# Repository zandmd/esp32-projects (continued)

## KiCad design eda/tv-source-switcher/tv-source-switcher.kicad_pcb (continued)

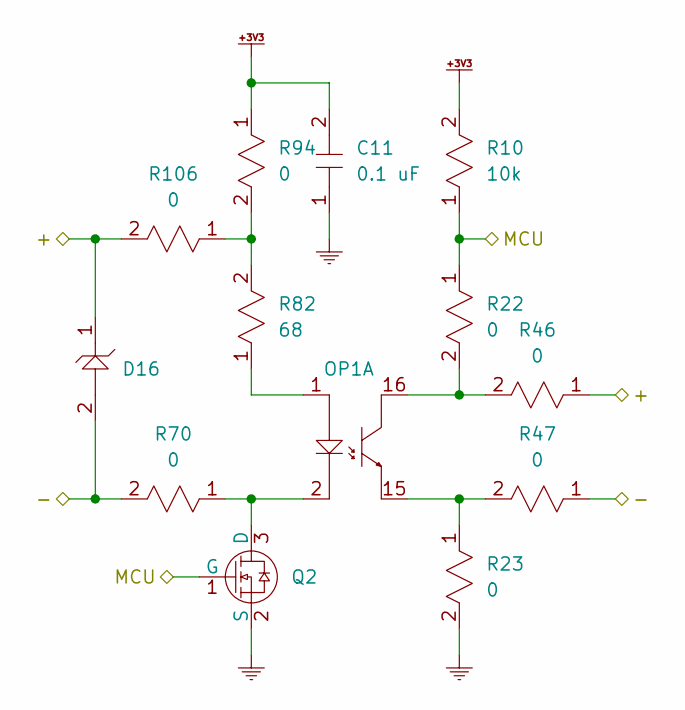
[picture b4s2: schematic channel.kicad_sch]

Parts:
C11: 0.1 uF; PASSIVE-NPOL-0805
D16: SMAJ5.0A
OP1: LTV-847S
Q2: BSS816NWH6327XTSA1
R10: 10k; PASSIVE-NPOL-0805
R22, R23, R46, R47, R70, R94, R106: 0; PASSIVE-NPOL-0805
R82: 68; PASSIVE-NPOL-0805

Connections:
+3V3: C11.2, R10.2, R94.1; also elsewhere on the board
/Channel 0/MCU: Q2.1 (G), R10.1, R22.1; also elsewhere on the board
GND: C11.1, Q2.2 (S), R23.2; also elsewhere on the board
unnamed: OP1.1 (A), R82.1
unnamed: OP1.16 (C), R22.2, R46.2
unnamed: OP1.15 (E), R23.1, R47.2
unnamed: OP1.2 (K), Q2.3 (D), R70.1
unnamed 52: OP1.3 (A); also elsewhere on the board
unnamed 53: OP1.14 (C); also elsewhere on the board
unnamed 54: OP1.13 (E); also elsewhere on the board
unnamed 55: OP1.4 (K); also elsewhere on the board
unnamed 56: OP1.5 (A); also elsewhere on the board
unnamed 57: OP1.12 (C); also elsewhere on the board
unnamed 58: OP1.11 (E); also elsewhere on the board
unnamed 59: OP1.6 (K); also elsewhere on the board
unnamed 60: OP1.7 (A); also elsewhere on the board
unnamed 61: OP1.10 (C); also elsewhere on the board
unnamed 62: OP1.9 (E); also elsewhere on the board
unnamed 63: OP1.8 (K); also elsewhere on the board
unnamed: R82.2, R94.2, R106.1

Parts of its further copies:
C12, C13, C14, C15, C16, C17, C18, C19, C20, C21, C22: 0.1 uF; PASSIVE-NPOL-0805
D5, D6, D7, D8, D9, D10, D11, D12, D13, D14, D15: SMAJ5.0A
OP2, OP3: LTV-847S
Q3, Q4, Q5, Q6, Q7, Q8, Q9, Q10, Q11, Q12, Q13: BSS816NWH6327XTSA1
R11, R12, R13, R14, R15, R16, R17, R18, R19, R20, R21: 10k; PASSIVE-NPOL-0805
R24, R25, R26, R27, R28, R29, R30, R31, R32, R33, R34, R35, R36, R37, R38, R39, R40, R41, R42, R43, R44, R45, R48, R49, R50, R51, R52, R53, R54, R55, R56, R57, R58, R59, R60, R61, R62, R63, R64, R65, R66, R67, R68, R69, R71, R72, R73, R74, R75, R76, R77, R78, R79, R80, R81, R95, R96, R97, R98, R99, R100, R101, R102, R103, R104, R105, R107, R108, R109, R110, R111, R112, R113, R114, R115, R116, R117: 0; PASSIVE-NPOL-0805
R83, R84, R85, R86, R87, R88, R89, R90, R91, R92, R93: 68; PASSIVE-NPOL-0805

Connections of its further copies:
+3V3: C12.2, C13.2, C14.2, C15.2, C16.2, C17.2, C18.2, C19.2, C20.2, C21.2, C22.2, R11.2, R12.2, R13.2, R14.2, R15.2, R16.2, R17.2, R18.2, R19.2, R20.2, R21.2, R95.1, R96.1, R97.1, R98.1, R99.1, R100.1, R101.1, R102.1, R103.1, R104.1, R105.1; also elsewhere on the board
/Channel 1/+: D6.1, R48.1, R107.2; also elsewhere on the board
/Channel 1/-: D6.2, R49.1, R71.2; also elsewhere on the board
/Channel 1/MCU: Q3.1 (G), R11.1, R24.1; also elsewhere on the board
/Channel 2/+: D7.1, R50.1, R108.2; also elsewhere on the board
/Channel 2/-: D7.2, R51.1, R72.2; also elsewhere on the board
/Channel 2/MCU: Q4.1 (G), R12.1, R26.1; also elsewhere on the board
/Channel 3/+: D8.1, R52.1, R109.2; also elsewhere on the board
/Channel 3/-: D8.2, R53.1, R73.2; also elsewhere on the board
/Channel 3/MCU: Q5.1 (G), R13.1, R28.1; also elsewhere on the board
/Channel 4/+: D9.1, R54.1, R110.2; also elsewhere on the board
/Channel 4/-: D9.2, R55.1, R74.2; also elsewhere on the board
/Channel 4/MCU: Q6.1 (G), R14.1, R30.1; also elsewhere on the board
/Channel 5/+: D10.1, R56.1, R111.2; also elsewhere on the board
/Channel 5/-: D10.2, R57.1, R75.2; also elsewhere on the board
/Channel 5/MCU: Q7.1 (G), R15.1, R32.1; also elsewhere on the board
/Channel 6/+: D11.1, R58.1, R112.2; also elsewhere on the board
/Channel 6/-: D11.2, R59.1, R76.2; also elsewhere on the board
/Channel 6/MCU: Q8.1 (G), R16.1, R34.1; also elsewhere on the board
/Channel 7/+: D12.1, R60.1, R113.2; also elsewhere on the board
/Channel 7/-: D12.2, R61.1, R77.2; also elsewhere on the board
/Channel 7/MCU: Q9.1 (G), R17.1, R36.1; also elsewhere on the board
/Channel 8/+: D13.1, R62.1, R114.2; also elsewhere on the board
/Channel 8/-: D13.2, R63.1, R78.2; also elsewhere on the board
/Channel 8/MCU: Q10.1 (G), R18.1, R38.1; also elsewhere on the board
/Channel 9/+: D14.1, R64.1, R115.2; also elsewhere on the board
/Channel 9/-: D14.2, R65.1, R79.2; also elsewhere on the board
/Channel 9/MCU: Q11.1 (G), R19.1, R40.1; also elsewhere on the board
/Channel 10/+: D15.1, R66.1, R116.2; also elsewhere on the board
/Channel 10/-: D15.2, R67.1, R80.2; also elsewhere on the board
/Channel 10/MCU: Q12.1 (G), R20.1, R42.1; also elsewhere on the board
/Channel 11/MCU: Q13.1 (G), R21.1, R44.1; also elsewhere on the board
GND: C12.1, C13.1, C14.1, C15.1, C16.1, C17.1, C18.1, C19.1, C20.1, C21.1, C22.1, Q3.2 (S), Q4.2 (S), Q5.2 (S), Q6.2 (S), Q7.2 (S), Q8.2 (S), Q9.2 (S), Q10.2 (S), Q11.2 (S), Q12.2 (S), Q13.2 (S), R25.2, R27.2, R29.2, R31.2, R33.2, R35.2, R37.2, R39.2, R41.2, R43.2, R45.2; also elsewhere on the board
unnamed 52: R83.1; also elsewhere on the board
unnamed 53: R24.2, R48.2; also elsewhere on the board
unnamed 54: R25.1, R49.2; also elsewhere on the board
unnamed 55: Q3.3 (D), R71.1; also elsewhere on the board
unnamed 56: R84.1; also elsewhere on the board
unnamed 57: R26.2, R50.2; also elsewhere on the board
unnamed 58: R27.1, R51.2; also elsewhere on the board
unnamed 59: Q4.3 (D), R72.1; also elsewhere on the board
unnamed 60: R85.1; also elsewhere on the board
unnamed 61: R28.2, R52.2; also elsewhere on the board
unnamed 62: R29.1, R53.2; also elsewhere on the board
unnamed 63: Q5.3 (D), R73.1; also elsewhere on the board
unnamed: OP2.1 (A), R86.1
unnamed: OP2.16 (C), R30.2, R54.2
unnamed: OP2.15 (E), R31.1, R55.2
unnamed: OP2.2 (K), Q6.3 (D), R74.1
unnamed: OP2.3 (A), R87.1
unnamed: OP2.14 (C), R32.2, R56.2
unnamed: OP2.13 (E), R33.1, R57.2
unnamed: OP2.4 (K), Q7.3 (D), R75.1
unnamed: OP2.5 (A), R88.1
unnamed: OP2.12 (C), R34.2, R58.2
unnamed: OP2.11 (E), R35.1, R59.2
unnamed: OP2.6 (K), Q8.3 (D), R76.1
unnamed: OP2.7 (A), R89.1
unnamed: OP2.10 (C), R36.2, R60.2
unnamed: OP2.9 (E), R37.1, R61.2
unnamed: OP2.8 (K), Q9.3 (D), R77.1
unnamed: OP3.1 (A), R90.1
unnamed: OP3.16 (C), R38.2, R62.2
unnamed: OP3.15 (E), R39.1, R63.2
unnamed: OP3.2 (K), Q10.3 (D), R78.1
unnamed: OP3.3 (A), R91.1
unnamed: OP3.14 (C), R40.2, R64.2
unnamed: OP3.13 (E), R41.1, R65.2
unnamed: OP3.4 (K), Q11.3 (D), R79.1
unnamed: OP3.5 (A), R92.1
unnamed: OP3.12 (C), R42.2, R66.2
unnamed: OP3.11 (E), R43.1, R67.2
unnamed: OP3.6 (K), Q12.3 (D), R80.1
unnamed: OP3.7 (A), R93.1
unnamed: OP3.10 (C), R44.2, R68.2
unnamed: OP3.9 (E), R45.1, R69.2
unnamed: OP3.8 (K), Q13.3 (D), R81.1
unnamed: R88.2, R100.2, R112.1
unnamed: R89.2, R101.2, R113.1
unnamed: R90.2, R102.2, R114.1
unnamed: R91.2, R103.2, R115.1
unnamed: R92.2, R104.2, R116.1
unnamed: R93.2, R105.2, R117.1
unnamed: R83.2, R95.2, R107.1
unnamed: R84.2, R96.2, R108.1
unnamed: R85.2, R97.2, R109.1
unnamed: R86.2, R98.2, R110.1
unnamed: R87.2, R99.2, R111.1

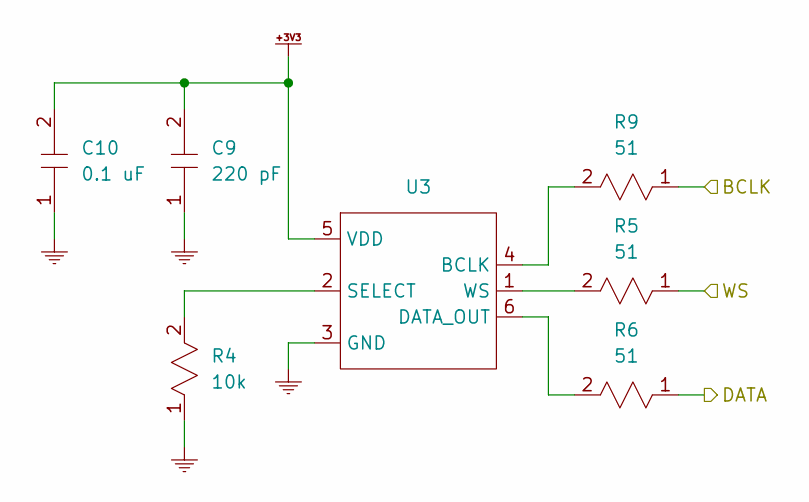
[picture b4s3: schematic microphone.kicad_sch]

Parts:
C9: 220 pF; PASSIVE-NPOL-0805
C10: 0.1 uF; PASSIVE-NPOL-0805
R4: 10k; PASSIVE-NPOL-0805
R5, R6, R9: 51; PASSIVE-NPOL-0805
U3: SPH0645LM4H-B

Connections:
+3V3: C9.2, C10.2, U3.5 (VDD); also elsewhere on the board
/Microcontroller/BCLK: R9.1; also elsewhere on the board
/Microcontroller/DIN: R6.1; also elsewhere on the board
/Microcontroller/WS: R5.1; also elsewhere on the board
GND: C9.1, C10.1, R4.1, U3.3 (GND); also elsewhere on the board
unnamed: R9.2, U3.4 (BCLK)
unnamed: R6.2, U3.6 (DATA_OUT)
unnamed: R4.2, U3.2 (SELECT)
unnamed: R5.2, U3.1 (WS)

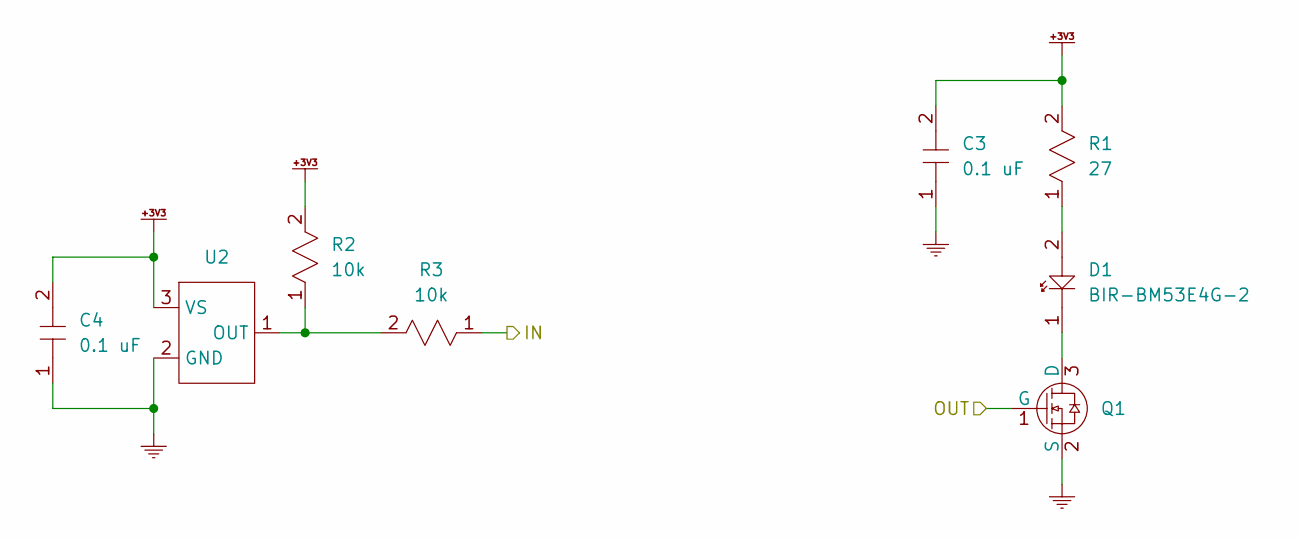
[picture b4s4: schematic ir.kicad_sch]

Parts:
C3, C4: 0.1 uF; PASSIVE-NPOL-0805
D1: BIR-BM53E4G-2; PASSIVE-POL-LED-5.7MM
Q1: BSS816NWH6327XTSA1
R1: 27; PASSIVE-NPOL-0805
R2, R3: 10k; PASSIVE-NPOL-0805
U2: TSOP38238

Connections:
+3V3: C3.2, C4.2, R1.2, R2.2, U2.3 (VS); also elsewhere on the board
/Infrared/IN: R3.1; also elsewhere on the board
/Infrared/OUT: Q1.1 (G); also elsewhere on the board
GND: C3.1, C4.1, Q1.2 (S), U2.2 (GND); also elsewhere on the board
unnamed: D1.2 (A), R1.1
unnamed: D1.1 (K), Q1.3 (D)
unnamed: R2.1, R3.2, U2.1 (OUT)

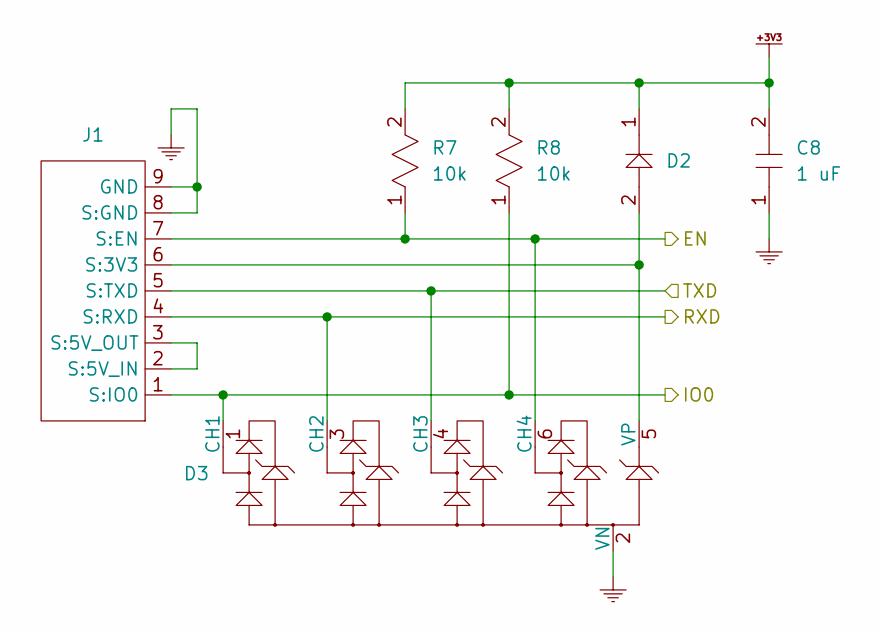
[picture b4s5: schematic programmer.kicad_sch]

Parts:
C8: 1 uF; PASSIVE-NPOL-0805
D2: PASSIVE-POL-0805
D3: CM1293A-04SO
J1: CF25081D0R0-10-NH
R7, R8: 10k; PASSIVE-NPOL-0805

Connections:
+3V3: C8.2, D2.1, R7.2, R8.2; also elsewhere on the board
/Microcontroller/EN: D3.6 (CH4), J1.7 (S:EN), R7.1; also elsewhere on the board
/Microcontroller/IO0: D3.1 (CH1), J1.1 (S:IO0), R8.1; also elsewhere on the board
/Microcontroller/RXD: D3.3 (CH2), J1.4 (S:RXD); also elsewhere on the board
/Microcontroller/TXD: D3.4 (CH3), J1.5 (S:TXD); also elsewhere on the board
GND: C8.1, D3.2 (VN), J1.8 (S:GND), J1.9 (GND); also elsewhere on the board
unnamed: D2.2, D3.5 (VP), J1.6 (S:3V3)
unnamed: J1.2 (S:5V_IN), J1.3 (S:5V_OUT)

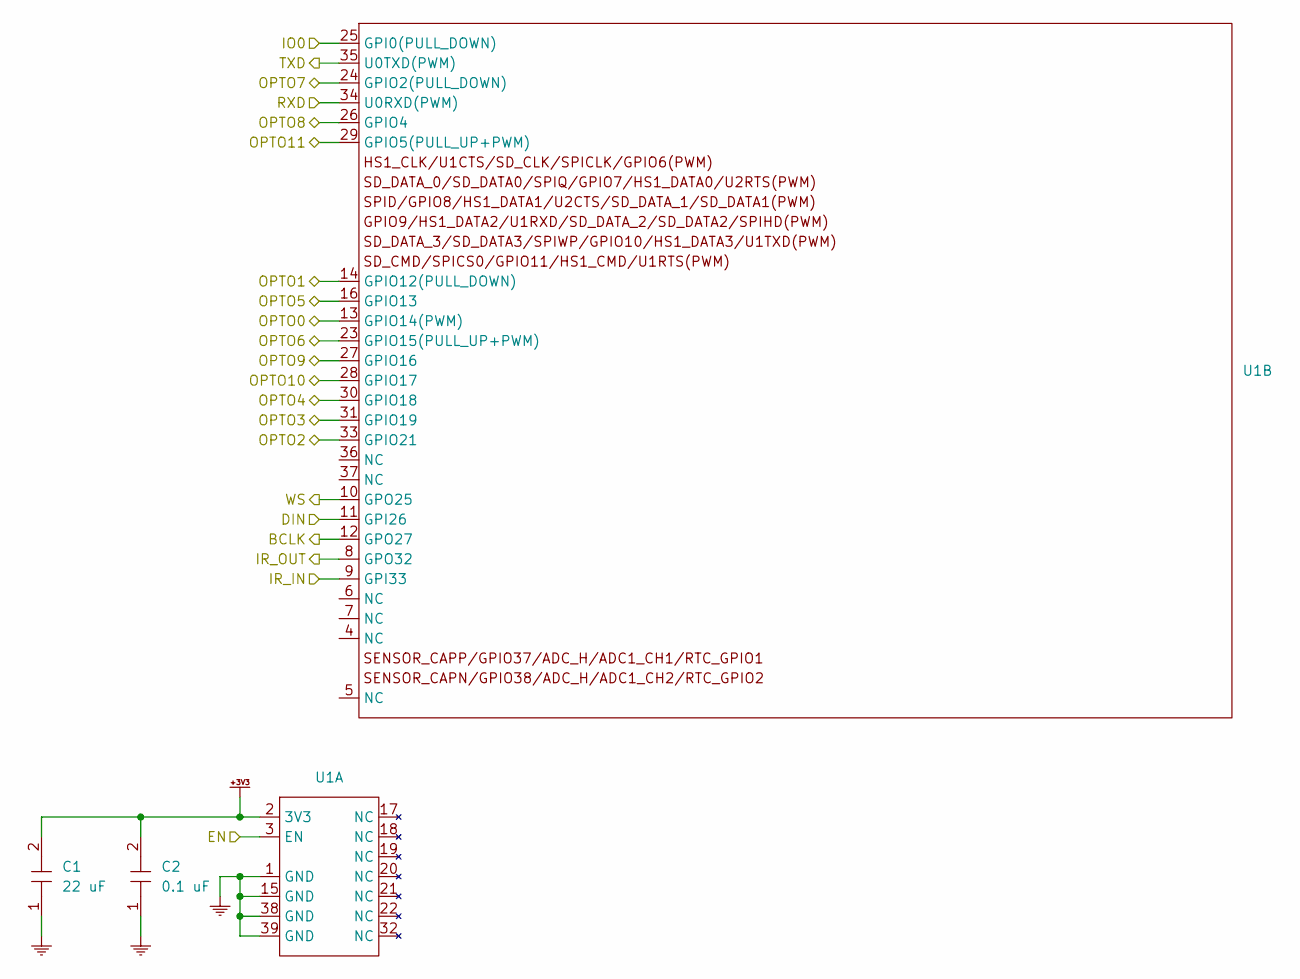
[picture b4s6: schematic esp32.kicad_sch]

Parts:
C1: 22 uF; PASSIVE-NPOL-0805
C2: 0.1 uF; PASSIVE-NPOL-0805
U1: ESP32-WROOM-32E-N4

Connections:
+3V3: C1.2, C2.2, U1.2 (3V3); also elsewhere on the board
/Channel 0/MCU: U1.13 (GPIO14(PWM)); also elsewhere on the board
/Channel 1/MCU: U1.14 (GPIO12(PULL_DOWN)); also elsewhere on the board
/Channel 2/MCU: U1.33 (GPIO21); also elsewhere on the board
/Channel 3/MCU: U1.31 (GPIO19); also elsewhere on the board
/Channel 4/MCU: U1.30 (GPIO18); also elsewhere on the board
/Channel 5/MCU: U1.16 (GPIO13); also elsewhere on the board
/Channel 6/MCU: U1.23 (GPIO15(PULL_UP+PWM)); also elsewhere on the board
/Channel 7/MCU: U1.24 (GPIO2(PULL_DOWN)); also elsewhere on the board
/Channel 8/MCU: U1.26 (GPIO4); also elsewhere on the board
/Channel 9/MCU: U1.27 (GPIO16); also elsewhere on the board
/Channel 10/MCU: U1.28 (GPIO17); also elsewhere on the board
/Channel 11/MCU: U1.29 (GPIO5(PULL_UP+PWM)); also elsewhere on the board
/Infrared/IN: U1.9 (GPI33); also elsewhere on the board
/Infrared/OUT: U1.8 (GPO32); also elsewhere on the board
/Microcontroller/BCLK: U1.12 (GPO27); also elsewhere on the board
/Microcontroller/DIN: U1.11 (GPI26); also elsewhere on the board
/Microcontroller/EN: U1.3 (EN); also elsewhere on the board
/Microcontroller/IO0: U1.25 (GPI0(PULL_DOWN)); also elsewhere on the board
/Microcontroller/RXD: U1.34 (U0RXD(PWM)); also elsewhere on the board
/Microcontroller/TXD: U1.35 (U0TXD(PWM)); also elsewhere on the board
/Microcontroller/WS: U1.10 (GPO25); also elsewhere on the board
GND: C1.1, C2.1, U1.1 (GND), U1.15 (GND), U1.38 (GND), U1.39 (GND); also elsewhere on the board

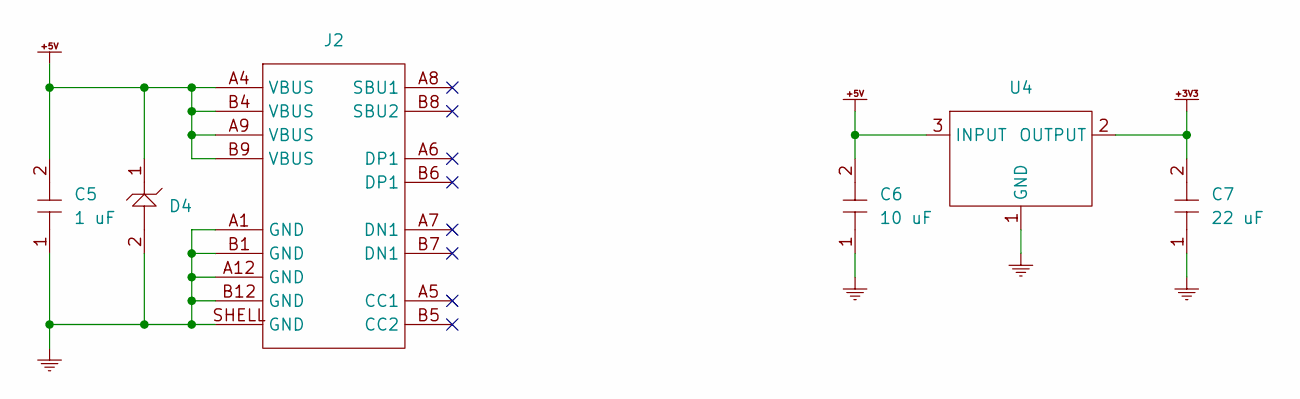
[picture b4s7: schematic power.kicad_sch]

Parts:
C5: 1 uF; PASSIVE-NPOL-0805
C6: 10 uF; PASSIVE-NPOL-0805
C7: 22 uF; PASSIVE-NPOL-0805
D4: SMAJ5.0A
J2: USB4520-03-0-A
U4: AZ1117IH-3.3TRG1

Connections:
+3V3: C7.2, U4.2 (OUTPUT); also elsewhere on the board
+5V: C5.2, C6.2, D4.1, J2.A4 (VBUS), J2.A9 (VBUS), J2.B4 (VBUS), J2.B9 (VBUS), U4.3 (INPUT)
GND: C5.1, C6.1, C7.1, D4.2, J2.A1 (GND), J2.A12 (GND), J2.B1 (GND), J2.B12 (GND), J2.SHELL (GND), U4.1 (GND); also elsewhere on the board

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
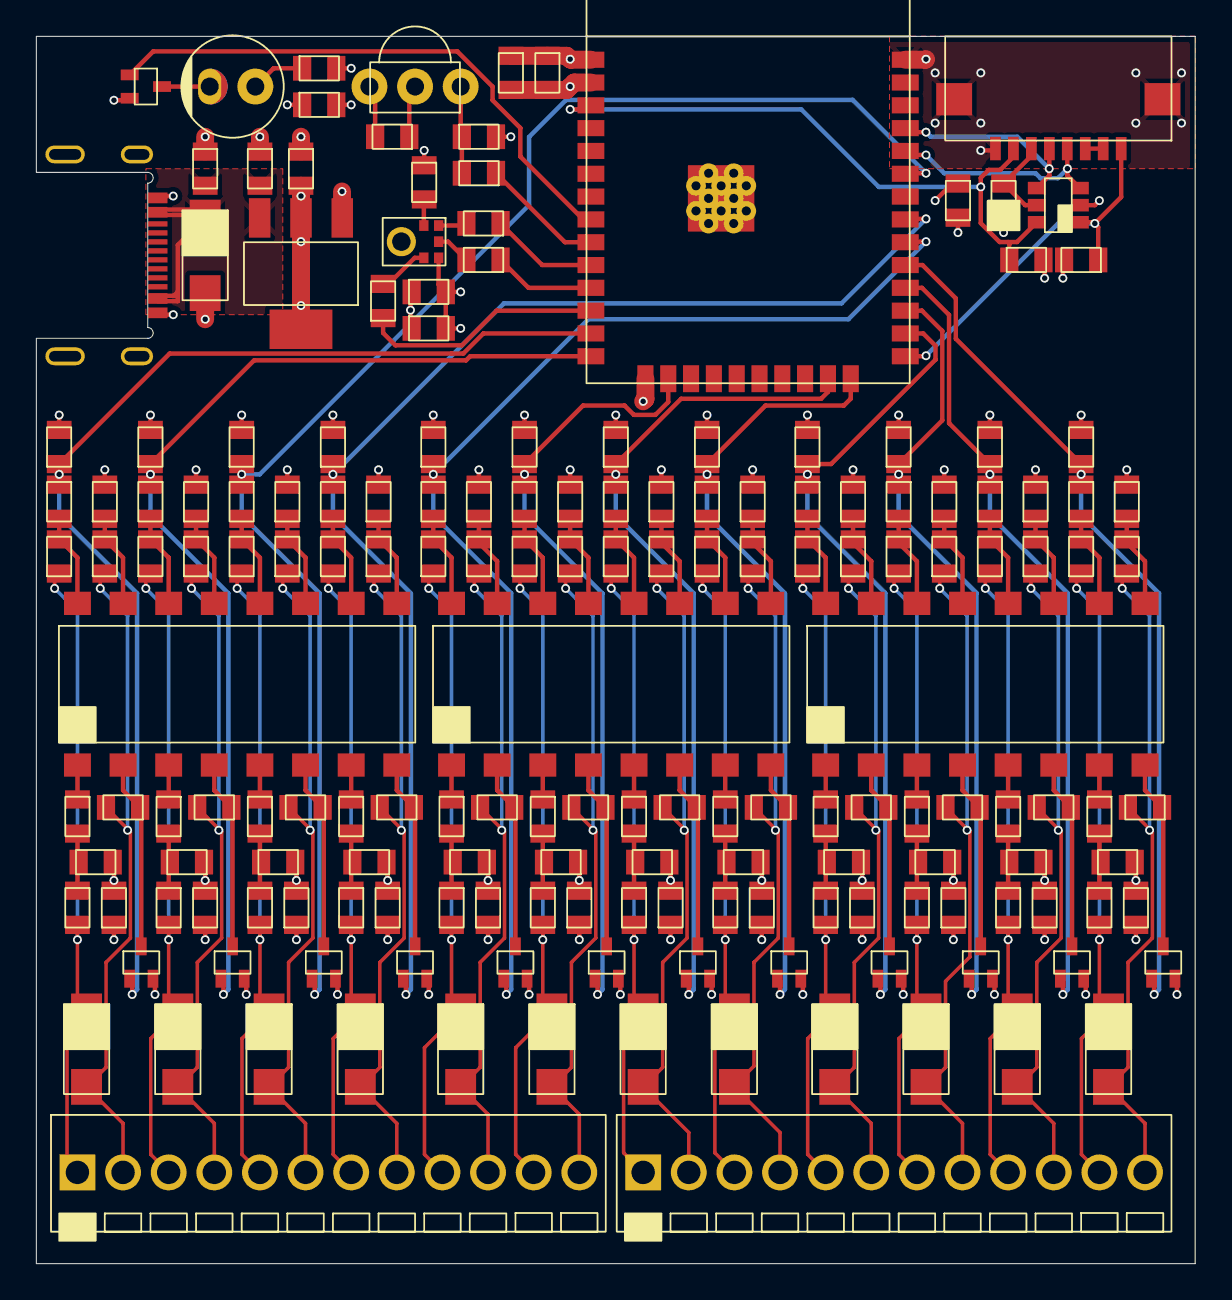
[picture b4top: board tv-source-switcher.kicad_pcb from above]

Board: 4 copper layers, 64.5 x 68.3 mm, 179 parts (0 on the bottom side), 117 nets.

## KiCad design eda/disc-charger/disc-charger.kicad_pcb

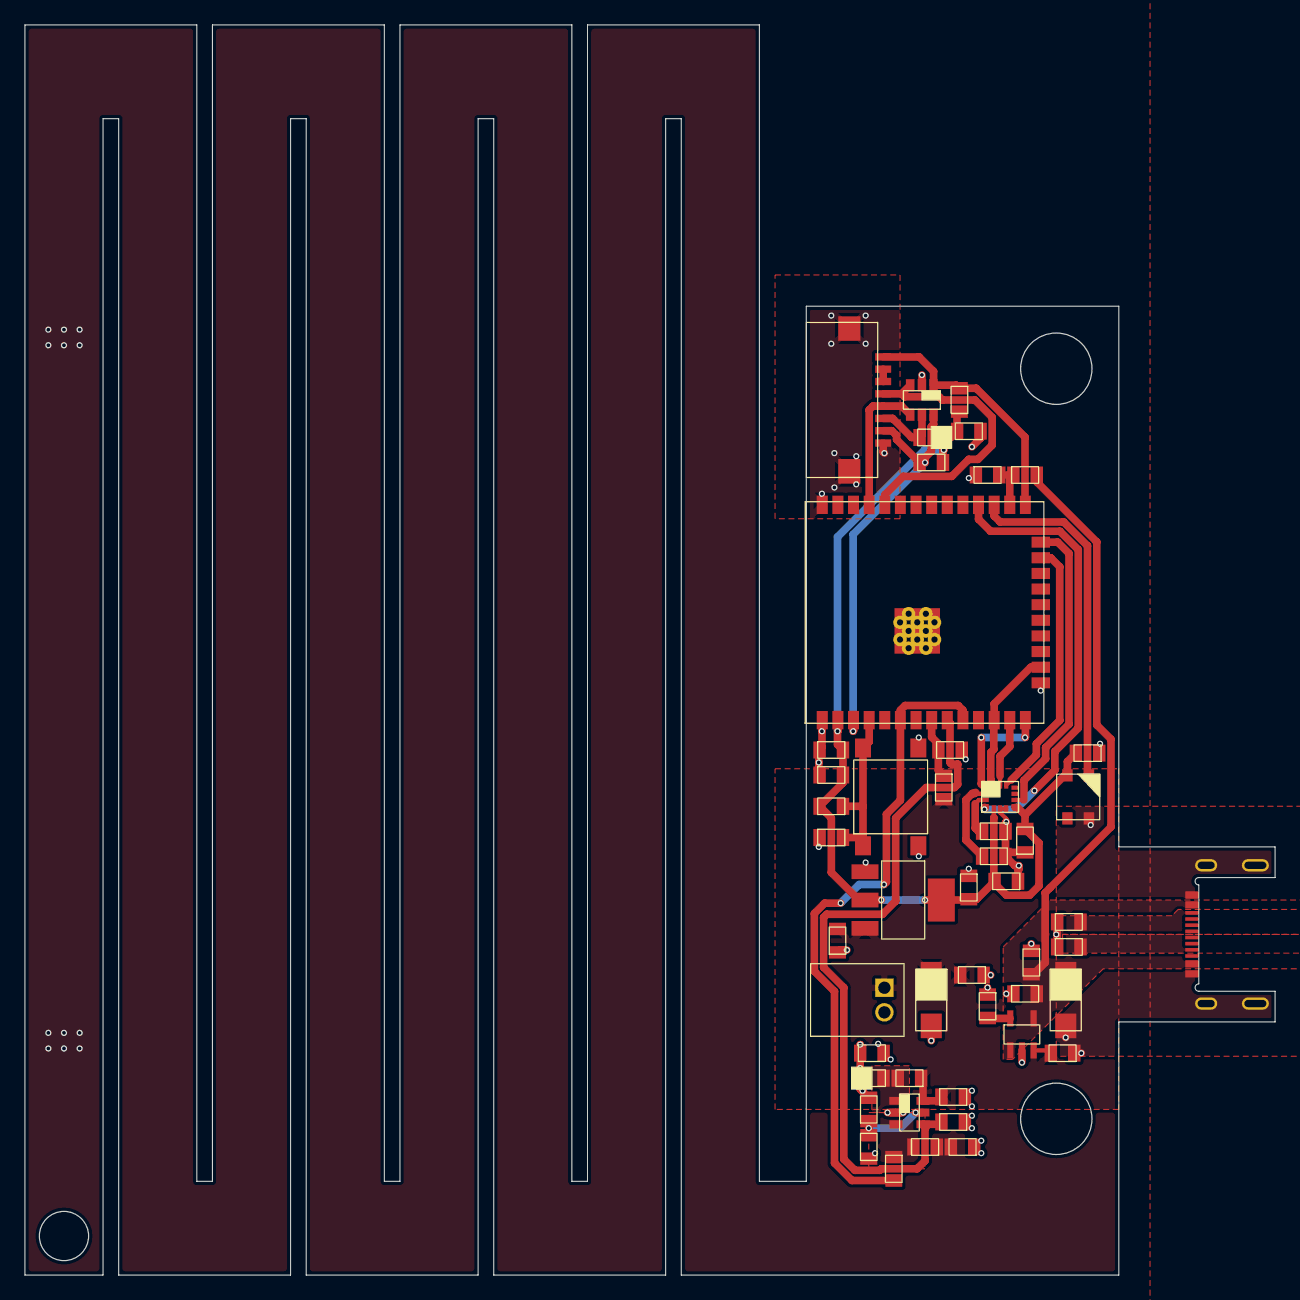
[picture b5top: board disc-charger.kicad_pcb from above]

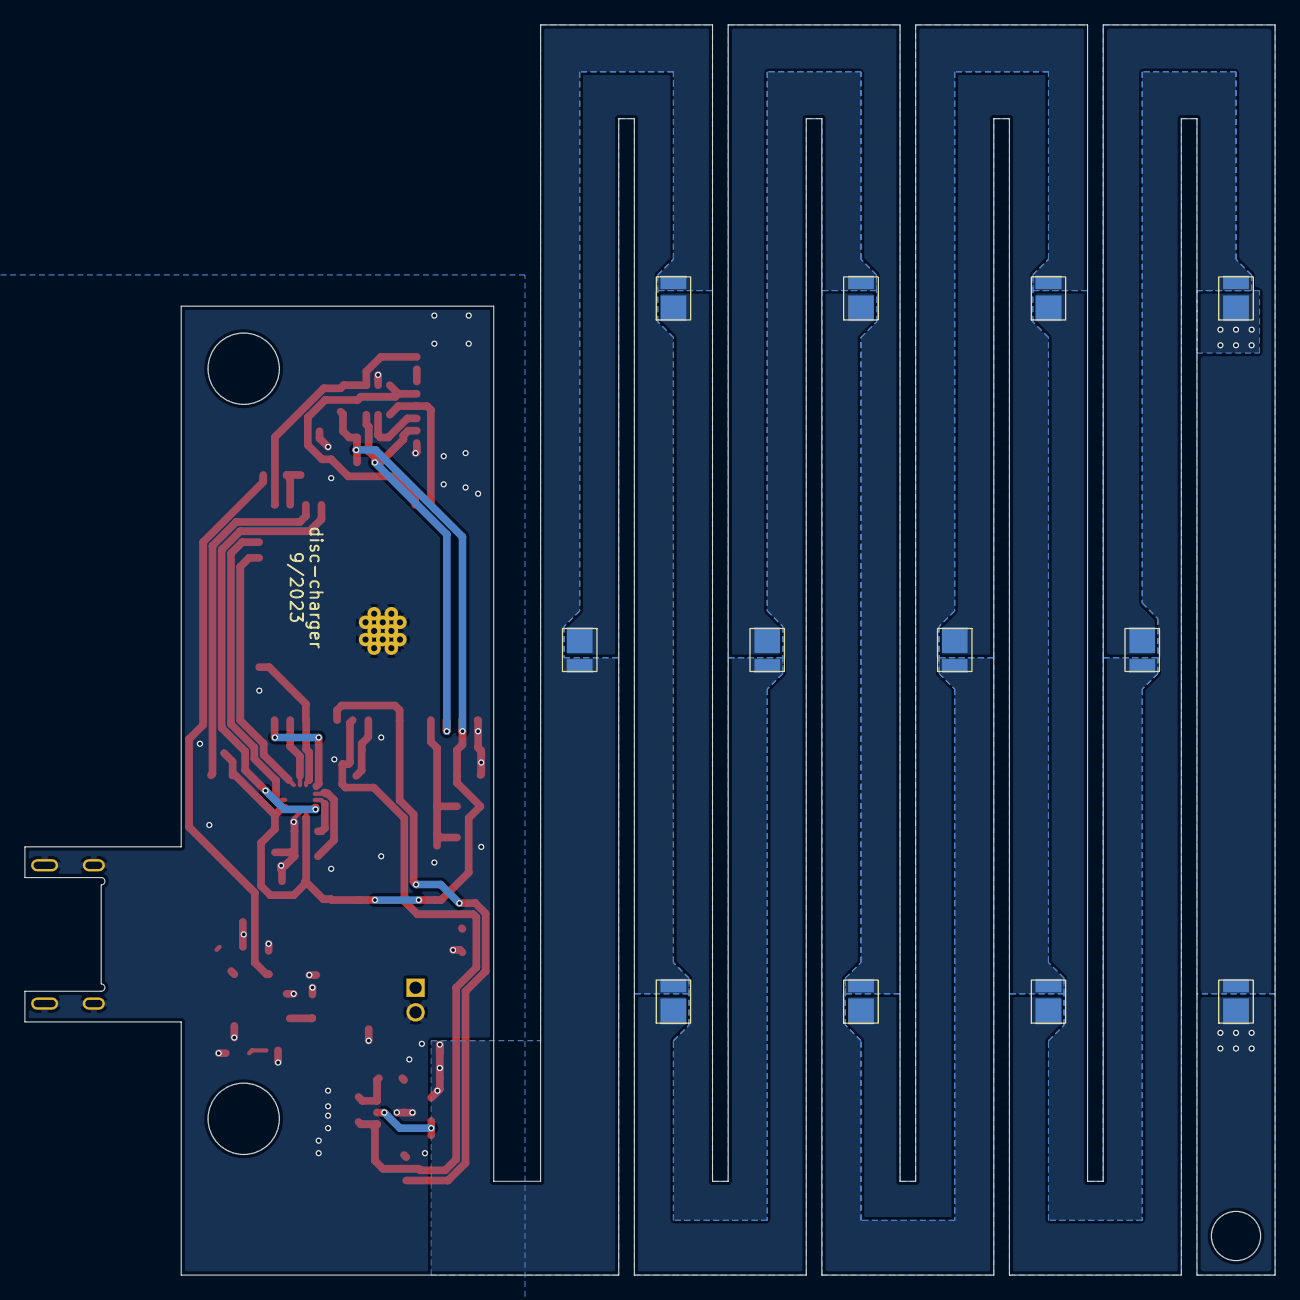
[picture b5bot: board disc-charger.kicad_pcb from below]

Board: 2 copper layers, 101.6 x 101.6 mm, 61 parts (12 on the bottom side), 42 nets.

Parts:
C1, C10, C11, C12, C13, C14: 1 uF; PASSIVE-NPOL-0805
C2, C3, C5, C6, C7: 0.1 uF; PASSIVE-NPOL-0805
C4, C8: 22 uF; PASSIVE-NPOL-0805
C9, C15: 10 uF; PASSIVE-NPOL-0805
D1: CM1293A-04SO
D2, D5: PASSIVE-POL-0805
D3, D4: SMAJ5.0A
D6, D7, D8, D9, D10, D11, D12, D13, D14, D15, D16, D17: 153283367A212; PASSIVE-POL-LED-153283367A212
J1: CF25081D0R0-10-NH
J2: USB4520-03-0-A
J3: S2B-PH-K-S
L1: 6.8 uH; PASSIVE-NPOL-0805
R1, R2, R3, R5, R7, R8, R9: 10k; PASSIVE-NPOL-0805
R4, R6, R10, R11, R16: 5.1k; PASSIVE-NPOL-0805
R12: 2.7k; PASSIVE-NPOL-0805
R13: 0; PASSIVE-NPOL-0805
R14, R18: 100k; PASSIVE-NPOL-0805
R15: R; PASSIVE-NPOL-0805
R17: 3.6; PASSIVE-NPOL-0805
S1: PTS645SM43SMTR92 LFS
U1: ESP32-WROOM-32E-N4
U2: LSM6DSOTR
U3: 2659
U4: AZ1117IH-3.3TRG1
U5: MCP73812T-420I/OT; MCP73812T-420IOT
U6: AP3032KTR-G1

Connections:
+3V3: C1.2, C2.2, C3.2, C4.2, C6.2, C7.2, C8.2, D2.1, R1.2, R2.2, R7.2, U1.2 (3V3), U2.5 (VDDIO), U2.8 (VDD), U3.4 (VDD), U4.2 (OUTPUT)
+5V: C10.2, C12.2, D4.1, J2.A4 (VBUS), J2.A9 (VBUS), J2.B4 (VBUS), J2.B9 (VBUS), R4.2, U5.1 (CE), U5.4 (VDD)
/LEDs/CTRL: R14.2, U1.9 (GPO33), U6.4 (CTRL)
/LEDs/DIM: R18.2, U1.6 (ADC1_CH6), U1.10 (GPO25)
/Microcontroller/5V: R3.2, R4.1, U1.26 (ADC2_CH0)
/Microcontroller/BAT: R5.2, R6.1, U1.8 (ADC1_CH4)
/Microcontroller/BTN: C5.2, R7.1, S1.1, S1.2, U1.4 (GPIO36)
/Microcontroller/CS: U1.23 (HSPIM.CS(PULL_UP+PWM)), U2.12 (CS)
/Microcontroller/EN: D1.6 (CH4), J1.7 (S:EN), R2.1, U1.3 (EN)
/Microcontroller/INT1: U1.28 (GPI17), U2.4 (INT1)
/Microcontroller/INT2: U1.24 (GPI2(PULL_DOWN)), U2.9 (INT2)
/Microcontroller/IO0: D1.1 (CH1), J1.1 (S:IO0), R1.1, U1.25 (GPI0(PULL_DOWN))
/Microcontroller/MISO: U1.14 (HSPIM.MISO(PULL_DOWN)), U2.1 (MISO)
/Microcontroller/MOSI: U1.12 (ADC2_CH7), U1.16 (HSPIM.MOSI), U2.14 (MOSI)
/Microcontroller/NEOPIXEL: U1.27 (GPO16), U3.3 (DIN)
/Microcontroller/RXD: D1.3 (CH2), J1.4 (S:RXD), U1.34 (U0RXD(PWM))
/Microcontroller/SCLK: U1.13 (HSPIM.SCLK(PWM)), U2.13 (SCL)
/Microcontroller/TXD: D1.4 (CH3), J1.5 (S:TXD), U1.35 (U0TXD(PWM))
GND: C1.1, C2.1, C3.1, C4.1, C5.1, C6.1, C7.1, C8.1, C9.1, C10.1, C11.1, C12.1, C13.1, C14.1, C15.1, D1.2 (VN), D3.2, D4.2, J1.8 (S:GND), J1.9 (GND), J2.A1 (GND), J2.A12 (GND), J2.B1 (GND), J2.B12 (GND), J2.SHELL (GND), J3.2 (-), R3.1, R5.1, R8.1, R9.1, R10.1, R11.1, R12.1, R14.1, R15.1, R17.1, S1.3, S1.4, U1.1 (GND), U1.15 (GND), U1.38 (GND), U1.39 (GND), U2.6 (GND), U2.7 (GND), U3.2 (VSS), U4.1 (GND), U5.2 (VSS), U6.2 (GND)
unnamed: D1.5 (VP), D2.2, J1.6 (S:3V3)
unnamed: C13.2, D5.1, D6.2 (A), D10.2 (A), R13.2
unnamed: D10.1 (K), D14.2 (A)
unnamed: D6.1 (K), D11.2 (A)
unnamed: D11.1 (K), D15.2 (A)
unnamed: D7.1 (K), D12.2 (A)
unnamed: D12.1 (K), D16.2 (A)
unnamed: D8.1 (K), D13.2 (A)
unnamed: D13.1 (K), D17.2 (A)
unnamed: D7.2 (A), D14.1 (K)
unnamed: D8.2 (A), D15.1 (K)
unnamed: D9.2 (A), D16.1 (K)
unnamed: D9.1 (K), D17.1 (K), R16.1, R17.2
unnamed: J1.2 (S:5V_IN), J1.3 (S:5V_OUT)
unnamed: J2.A5 (CC1), R11.2
unnamed: J2.B5 (CC2), R10.2
unnamed: R8.2, U2.3 (SCx)
unnamed: R9.2, U2.2 (SDx)
unnamed: R12.2, U5.5 (PROG)
unnamed: R16.2, R18.1, U6.3 (FB)
unnamed: R13.1, R15.2, U6.5 (OV)
unnamed: D5.2, L1.2, U6.1 (SW)
VBAT: C9.2, C11.2, C14.2, C15.2, D3.1, J3.1 (+), L1.1, R6.2, U4.3 (INPUT), U5.3 (VBAT), U6.6 (VIN)

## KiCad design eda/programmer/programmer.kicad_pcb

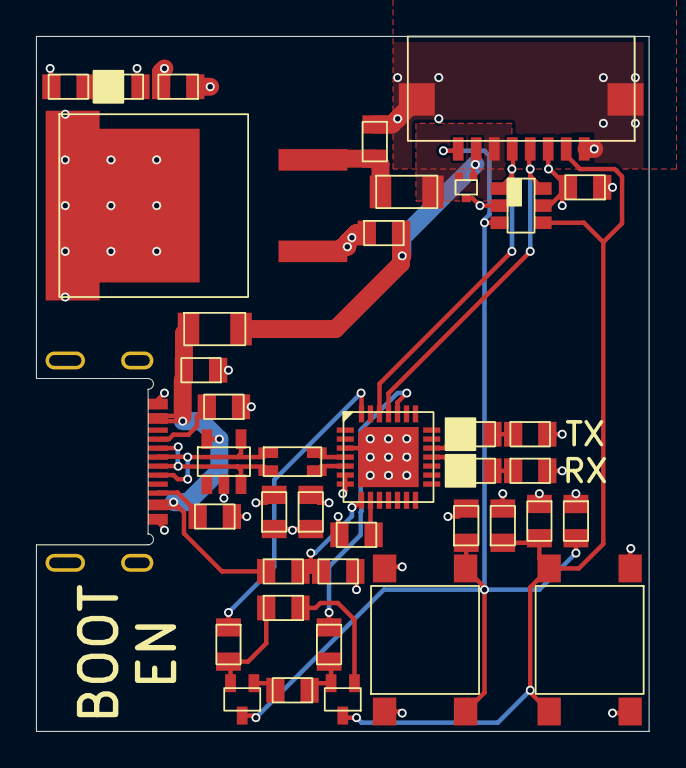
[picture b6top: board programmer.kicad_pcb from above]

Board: 4 copper layers, 34.0 x 38.6 mm, 40 parts (0 on the bottom side), 29 nets.

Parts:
C1: 22 uF; PASSIVE-NPOL-0805
C2: 10 uF; PASSIVE-NPOL-0805
C3, C4, C5: 1 uF; PASSIVE-NPOL-0805
C6: 4.7 uF; PASSIVE-NPOL-0805
C7, C8, C9: 0.1 uF; PASSIVE-NPOL-0805
D1: RED; PASSIVE-POL-0805
D2: DF3A6.8LFV,L3F
D3: CM1293A-04SO
D4: YELLOW; PASSIVE-POL-0805
D5: 824011
D6: ORANGE; PASSIVE-POL-0805
F1, F2: 3 A; PASSIVE-NPOL-1206
J1: CF25081D0R0-10-NH
J2: USB4520-03-0-A
Q1, Q2: BSS816NWH6327XTSA1
R1, R3, R4: 330; PASSIVE-NPOL-0805
R2, R5: 5.1k; PASSIVE-NPOL-0805
R6, R7: 100k; PASSIVE-NPOL-0805
R8, R11, R14: 10k; PASSIVE-NPOL-0805
R9: 22k; PASSIVE-NPOL-0805
R10: 47k; PASSIVE-NPOL-0805
R12, R13: 100; PASSIVE-NPOL-0805
S1, S2: PTS645SM43SMTR92 LFS
T1: 744232090
U1: AZ1084CS2-3.3TRE1
U2: CP2102N-A02-GQFN28

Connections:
+3V3: C1.2, C3.2, C6.2, C7.2, D1.2, D3.5 (VP), J1.3 (M:3V3), R3.2, R4.2, R6.2, R7.2, R8.2, U1.2 (OUTPUT), U2.6 (VDD), U2.7 (VREGIN)
+5V: C4.2, D2.1 (K1), F2.2, J1.7 (M:5V_OUT)
/Interface/EN: C8.2, D3.4 (CH3), J1.2 (M:EN), Q2.3 (D), R7.1, S2.3, S2.4
/Interface/IO0: C9.2, D3.3 (CH2), J1.8 (M:IO0), Q1.3 (D), R6.1, S1.3, S1.4
/Interface/RXD: D3.6 (CH4), J1.4 (M:TXD), U2.25 (RXD)
/Interface/TXD: D3.1 (CH1), J1.5 (M:RXD), U2.26 (TXD)
/Reset Logic/~DTR: R12.1, U2.28 (~DTR)
/Reset Logic/~RTS: R13.1, U2.24 (~RTS)
/UART/D+: T1.2, U2.4 (D+)
/UART/D-: T1.3, U2.5 (D-)
GND: C1.1, C2.1, C3.1, C4.1, C5.1, C6.1, C7.1, C8.1, C9.1, D2.3 (A), D3.2 (VN), D5.2 (GND), J1.1 (M:GND), J1.9 (GND), J2.A1 (GND), J2.A12 (GND), J2.B1 (GND), J2.B12 (GND), J2.SHELL (GND), R1.1, R2.1, R5.1, R10.1, S1.1, S1.2, S2.1, S2.2, U1.1 (GND), U2.3 (GND), U2.29 (GND)
unnamed: D1.1, R1.2
unnamed: D2.2 (K2), F1.2, J1.6 (M:5V_IN)
unnamed: D4.2 (A), R3.1
unnamed: D4.1 (K), U2.19 (~TXT)
unnamed: D5.3 (IO1), J2.A7 (DN1), J2.B7 (DN1), T1.4
unnamed: D5.4 (IO2), J2.A6 (DP1), J2.B6 (DP1), T1.1
unnamed: D6.2 (A), R4.1
unnamed: D6.1 (K), U2.18 (~RXT)
unnamed: J2.A5 (CC1), R2.2
unnamed: J2.B5 (CC2), R5.2
unnamed: Q1.1 (G), R14.2
unnamed: Q1.2 (S), R11.1, R12.2
unnamed: Q2.1 (G), R11.2
unnamed: Q2.2 (S), R13.2, R14.1
unnamed: C2.2, F1.1, U1.3 (INPUT)
unnamed: R9.1, R10.2, U2.8 (VBUS)
unnamed: R8.1, U2.9 (~RST)
VBUS: C5.2, D5.5 (VDD), F2.1, J2.A4 (VBUS), J2.A9 (VBUS), J2.B4 (VBUS), J2.B9 (VBUS), R9.2

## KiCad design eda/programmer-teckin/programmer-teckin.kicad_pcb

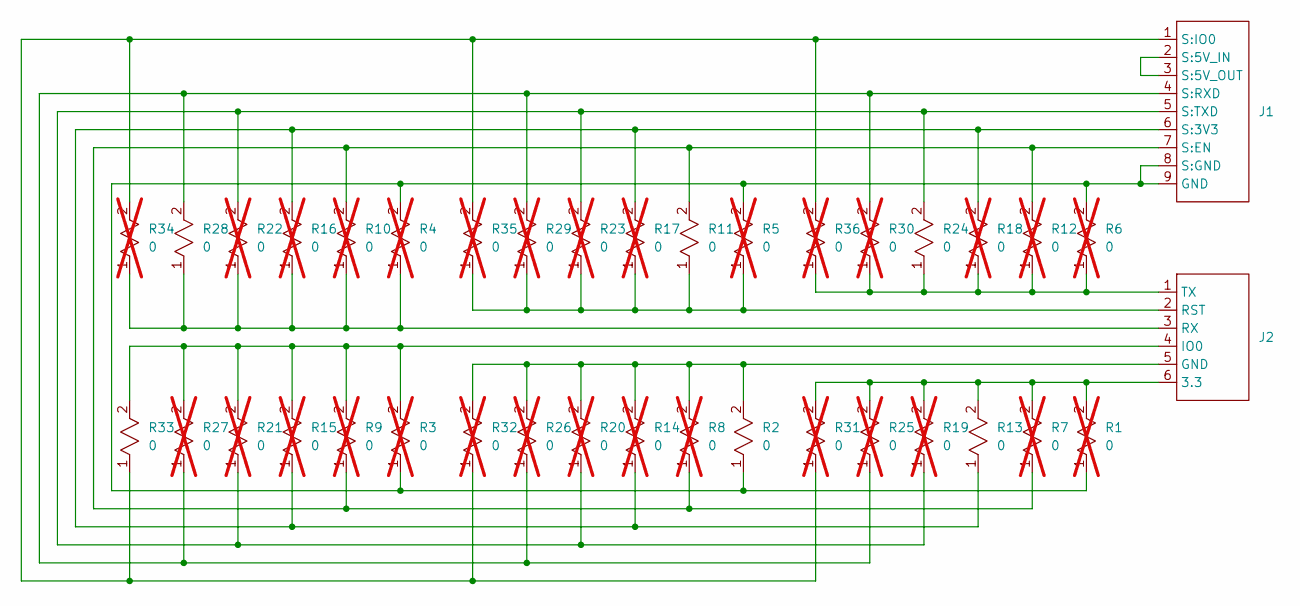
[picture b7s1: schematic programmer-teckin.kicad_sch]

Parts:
J1: CF25081D0R0-10-NH
J2: PH2-06-UA
R1, R3, R4, R5, R6, R7, R8, R9, R10, R12, R14, R15, R16, R17, R18, R19, R20, R21, R22, R23, R25, R26, R27, R29, R30, R31, R32, R34, R35, R36: 0; PASSIVE-NPOL-0805; not fitted
R2, R11, R13, R24, R28, R33: 0; PASSIVE-NPOL-0805

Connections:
unnamed: J1.8 (S:GND), J1.9 (GND), R1.1, R2.1, R3.1, R4.2, R5.2, R6.2
unnamed: J1.1 (S:IO0), R31.1, R32.1, R33.1, R34.2, R35.2, R36.2
unnamed: J1.2 (S:5V_IN), J1.3 (S:5V_OUT)
unnamed: J1.4 (S:RXD), R25.1, R26.1, R27.1, R28.2, R29.2, R30.2
unnamed: J1.5 (S:TXD), R19.1, R20.1, R21.1, R22.2, R23.2, R24.2
unnamed: J1.6 (S:3V3), R13.1, R14.1, R15.1, R16.2, R17.2, R18.2
unnamed: J1.7 (S:EN), R7.1, R8.1, R9.1, R10.2, R11.2, R12.2
unnamed: J2.1 (TX), R6.1, R12.1, R18.1, R24.1, R30.1, R36.1
unnamed: J2.2 (RST), R5.1, R11.1, R17.1, R23.1, R29.1, R35.1
unnamed: J2.3 (RX), R4.1, R10.1, R16.1, R22.1, R28.1, R34.1
unnamed: J2.4 (IO0), R3.2, R9.2, R15.2, R21.2, R27.2, R33.2
unnamed: J2.5 (GND), R2.2, R8.2, R14.2, R20.2, R26.2, R32.2
unnamed: J2.6 (3.3), R1.2, R7.2, R13.2, R19.2, R25.2, R31.2

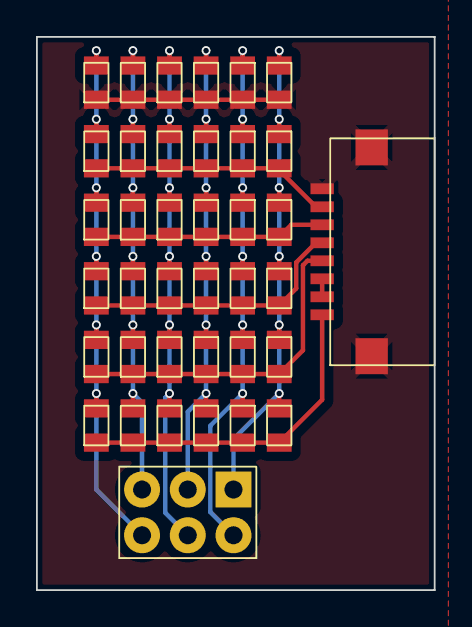
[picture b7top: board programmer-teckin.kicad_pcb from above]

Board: 2 copper layers, 22.1 x 30.7 mm, 38 parts (0 on the bottom side), 13 nets.
